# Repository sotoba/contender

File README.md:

# contender25

numpad for hardboot.

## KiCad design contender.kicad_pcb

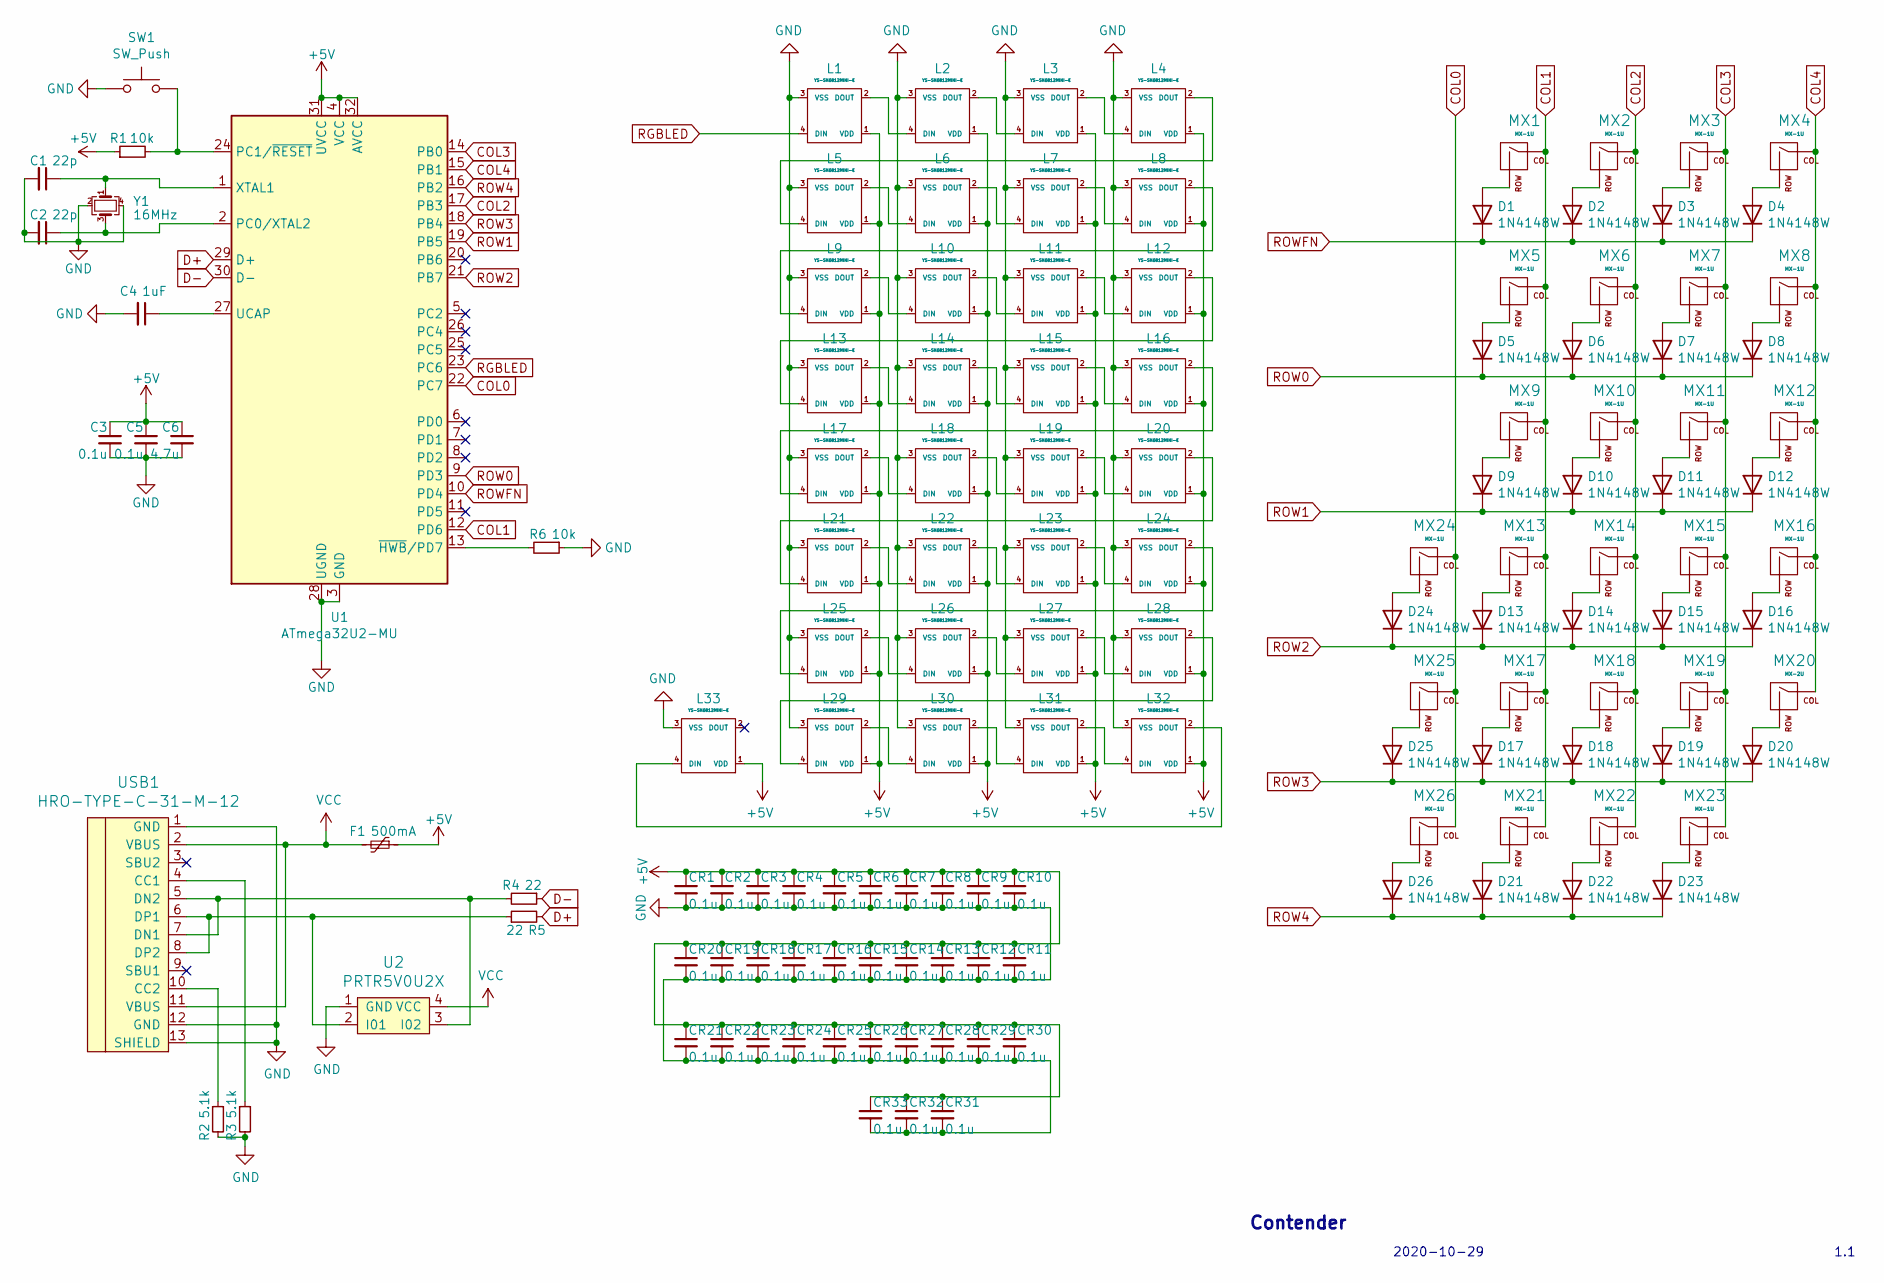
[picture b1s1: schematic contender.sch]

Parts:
C1, C2: 22p; C_0603_1608Metric
C3, C5: 0.1u; C_0603_1608Metric
C4: 1uF; C_0603_1608Metric
C6: 4.7u; C_0603_1608Metric
CR1, CR2, CR3, CR4, CR5, CR6, CR7, CR8, CR9, CR10, CR11, CR12, CR13, CR14, CR15, CR16, CR17, CR18, CR19, CR20, CR21, CR22, CR23, CR24, CR25, CR26, CR27, CR28, CR29, CR30, CR31, CR32, CR33: 0.1u; C_0603_1608Metric
D1, D2, D3, D4, D5, D6, D7, D8, D9, D10, D11, D12, D13, D14, D15, D16, D17, D18, D19, D20, D21, D22, D23, D24, D25, D26: 1N4148W; D_SOD-123
F1: 500mA; Fuse_1206_3216Metric
L1, L2, L3, L4, L5, L6, L7, L8, L9, L10, L11, L12, L13, L14, L15, L16, L17, L18, L19, L20, L21, L22, L23, L24, L25, L26, L27, L28, L29, L30, L31, L32, L33: YS-SK6812MINI-E; YS-SK6812-MINI-E_backlight
MX1, MX2, MX3, MX4, MX5, MX6, MX7, MX8, MX9, MX10, MX11, MX12, MX13, MX14, MX15, MX16, MX17, MX18, MX19, MX21, MX22, MX23, MX24, MX25, MX26: MX-1U; MXOnly-1U-Hotswap
MX20: MX-2U; MXOnly-2U-Hotswap-ReversedStabilizers
R1, R6: 10k; R_0805_2012Metric
R2, R3: 5.1k; R_0805_2012Metric
R4, R5: 22; R_0805_2012Metric
SW1: SW_Push; SKQG-1155865
U1: ATmega32U2-MU; QFN-32-1EP_5x5mm_Pitch0.5mm
U2: PRTR5V0U2X; SOT143B
USB1: HRO-TYPE-C-31-M-12; HRO-TYPE-C-31-M-12-Assembly
Y1: 16MHz; Crystal_SMD_3225-4Pin_3.2x2.5mm

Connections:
+5V: C3.1, C5.1, C6.1, CR1.1, CR2.1, CR3.1, CR4.1, CR5.1, CR6.1, CR7.1, CR8.1, CR9.1, CR10.1, CR11.1, CR12.1, CR13.1, CR14.1, CR15.1, CR16.1, CR17.1, CR18.1, CR19.1, CR20.1, CR21.1, CR22.1, CR23.1, CR24.1, CR25.1, CR26.1, CR27.1, CR28.1, CR29.1, CR30.1, CR31.1, CR32.1, CR33.1, F1.1, L1.1 (VDD), L2.1 (VDD), L3.1 (VDD), L4.1 (VDD), L5.1 (VDD), L6.1 (VDD), L7.1 (VDD), L8.1 (VDD), L9.1 (VDD), L10.1 (VDD), L11.1 (VDD), L12.1 (VDD), L13.1 (VDD), L14.1 (VDD), L15.1 (VDD), L16.1 (VDD), L17.1 (VDD), L18.1 (VDD), L19.1 (VDD), L20.1 (VDD), L21.1 (VDD), L22.1 (VDD), L23.1 (VDD), L24.1 (VDD), L25.1 (VDD), L26.1 (VDD), L27.1 (VDD), L28.1 (VDD), L29.1 (VDD), L30.1 (VDD), L31.1 (VDD), L32.1 (VDD), L33.1 (VDD), R1.1, U1.4 (VCC), U1.31 (UVCC), U1.32 (AVCC)
COL0: MX24.1 (COL), MX25.1 (COL), MX26.1 (COL), U1.22 (PC7)
COL1: MX1.1 (COL), MX5.1 (COL), MX9.1 (COL), MX13.1 (COL), MX17.1 (COL), MX21.1 (COL), U1.12 (PD6)
COL2: MX2.1 (COL), MX6.1 (COL), MX10.1 (COL), MX14.1 (COL), MX18.1 (COL), MX22.1 (COL), U1.17 (PB3)
COL3: MX3.1 (COL), MX7.1 (COL), MX11.1 (COL), MX15.1 (COL), MX19.1 (COL), MX23.1 (COL), U1.14 (PB0)
COL4: MX4.1 (COL), MX8.1 (COL), MX12.1 (COL), MX16.1 (COL), MX20.1 (COL), U1.15 (PB1)
D+: R5.2, U1.29 (D+)
D-: R4.1, U1.30 (D-)
GND: C1.2, C2.2, C3.2, C4.2, C5.2, C6.2, CR1.2, CR2.2, CR3.2, CR4.2, CR5.2, CR6.2, CR7.2, CR8.2, CR9.2, CR10.2, CR11.2, CR12.2, CR13.2, CR14.2, CR15.2, CR16.2, CR17.2, CR18.2, CR19.2, CR20.2, CR21.2, CR22.2, CR23.2, CR24.2, CR25.2, CR26.2, CR27.2, CR28.2, CR29.2, CR30.2, CR31.2, CR32.2, CR33.2, L1.3 (VSS), L2.3 (VSS), L3.3 (VSS), L4.3 (VSS), L5.3 (VSS), L6.3 (VSS), L7.3 (VSS), L8.3 (VSS), L9.3 (VSS), L10.3 (VSS), L11.3 (VSS), L12.3 (VSS), L13.3 (VSS), L14.3 (VSS), L15.3 (VSS), L16.3 (VSS), L17.3 (VSS), L18.3 (VSS), L19.3 (VSS), L20.3 (VSS), L21.3 (VSS), L22.3 (VSS), L23.3 (VSS), L24.3 (VSS), L25.3 (VSS), L26.3 (VSS), L27.3 (VSS), L28.3 (VSS), L29.3 (VSS), L30.3 (VSS), L31.3 (VSS), L32.3 (VSS), L33.3 (VSS), R2.2, R3.2, R6.1, SW1.1, U1.3 (GND), U1.28 (UGND), U1.33 (GND), U2.1 (GND), USB1.1 (GND), USB1.12 (GND), USB1.13 (SHIELD), Y1.2, Y1.4
unnamed: C1.1, U1.1 (XTAL1), Y1.1
unnamed: C2.1, U1.2 (PC0/XTAL2), Y1.3
unnamed: C4.1, U1.27 (UCAP)
unnamed: D1.2 (A), MX1.2 (ROW)
unnamed: D2.2 (A), MX2.2 (ROW)
unnamed: D3.2 (A), MX3.2 (ROW)
unnamed: D4.2 (A), MX4.2 (ROW)
unnamed: D5.2 (A), MX5.2 (ROW)
unnamed: D6.2 (A), MX6.2 (ROW)
unnamed: D7.2 (A), MX7.2 (ROW)
unnamed: D8.2 (A), MX8.2 (ROW)
unnamed: D9.2 (A), MX9.2 (ROW)
unnamed: D10.2 (A), MX10.2 (ROW)
unnamed: D11.2 (A), MX11.2 (ROW)
unnamed: D12.2 (A), MX12.2 (ROW)
unnamed: D13.2 (A), MX13.2 (ROW)
unnamed: D14.2 (A), MX14.2 (ROW)
unnamed: D15.2 (A), MX15.2 (ROW)
unnamed: D16.2 (A), MX16.2 (ROW)
unnamed: D17.2 (A), MX17.2 (ROW)
unnamed: D18.2 (A), MX18.2 (ROW)
unnamed: D19.2 (A), MX19.2 (ROW)
unnamed: D20.2 (A), MX20.2 (ROW)
unnamed: D21.2 (A), MX21.2 (ROW)
unnamed: D22.2 (A), MX22.2 (ROW)
unnamed: D23.2 (A), MX23.2 (ROW)
unnamed: D24.2 (A), MX24.2 (ROW)
unnamed: D25.2 (A), MX25.2 (ROW)
unnamed: D26.2 (A), MX26.2 (ROW)
unnamed: L1.2 (DOUT), L2.4 (DIN)
unnamed: L2.2 (DOUT), L3.4 (DIN)
unnamed: L3.2 (DOUT), L4.4 (DIN)
unnamed: L4.2 (DOUT), L5.4 (DIN)
unnamed: L5.2 (DOUT), L6.4 (DIN)
unnamed: L6.2 (DOUT), L7.4 (DIN)
unnamed: L7.2 (DOUT), L8.4 (DIN)
unnamed: L8.2 (DOUT), L9.4 (DIN)
unnamed: L10.2 (DOUT), L11.4 (DIN)
unnamed: L9.2 (DOUT), L10.4 (DIN)
unnamed: L11.2 (DOUT), L12.4 (DIN)
unnamed: L12.2 (DOUT), L13.4 (DIN)
unnamed: L13.2 (DOUT), L14.4 (DIN)
unnamed: L14.2 (DOUT), L15.4 (DIN)
unnamed: L15.2 (DOUT), L16.4 (DIN)
unnamed: L16.2 (DOUT), L17.4 (DIN)
unnamed: L17.2 (DOUT), L18.4 (DIN)
unnamed: L18.2 (DOUT), L19.4 (DIN)
unnamed: L19.2 (DOUT), L20.4 (DIN)
unnamed: L20.2 (DOUT), L21.4 (DIN)
unnamed: L21.2 (DOUT), L22.4 (DIN)
unnamed: L22.2 (DOUT), L23.4 (DIN)
unnamed: L23.2 (DOUT), L24.4 (DIN)
unnamed: L24.2 (DOUT), L25.4 (DIN)
unnamed: L25.2 (DOUT), L26.4 (DIN)
unnamed: L26.2 (DOUT), L27.4 (DIN)
unnamed: L27.2 (DOUT), L28.4 (DIN)
unnamed: L28.2 (DOUT), L29.4 (DIN)
unnamed: L29.2 (DOUT), L30.4 (DIN)
unnamed: L30.2 (DOUT), L31.4 (DIN)
unnamed: L31.2 (DOUT), L32.4 (DIN)
unnamed: L32.2 (DOUT), L33.4 (DIN)
unnamed: R1.2, SW1.2, U1.24 (PC1/~RESET)
unnamed: R2.1, USB1.10 (CC2)
unnamed: R3.1, USB1.4 (CC1)
unnamed: R4.2, U2.3 (I02), USB1.5 (DN2), USB1.7 (DN1)
unnamed: R5.1, U2.2 (I01), USB1.6 (DP1), USB1.8 (DP2)
unnamed: R6.2, U1.13 (~HWB~/PD7)
RGBLED: L1.4 (DIN), U1.23 (PC6)
ROW0: D5.1 (K), D6.1 (K), D7.1 (K), D8.1 (K), U1.9 (PD3)
ROW1: D9.1 (K), D10.1 (K), D11.1 (K), D12.1 (K), U1.19 (PB5)
ROW2: D13.1 (K), D14.1 (K), D15.1 (K), D16.1 (K), D24.1 (K), U1.21 (PB7)
ROW3: D17.1 (K), D18.1 (K), D19.1 (K), D20.1 (K), D25.1 (K), U1.18 (PB4)
ROW4: D21.1 (K), D22.1 (K), D23.1 (K), D26.1 (K), U1.16 (PB2)
ROWFN: D1.1 (K), D2.1 (K), D3.1 (K), D4.1 (K), U1.10 (PD4)
VCC: F1.2, U2.4 (VCC), USB1.2 (VBUS), USB1.11 (VBUS)

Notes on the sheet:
Contender
2020-10-29
1.1

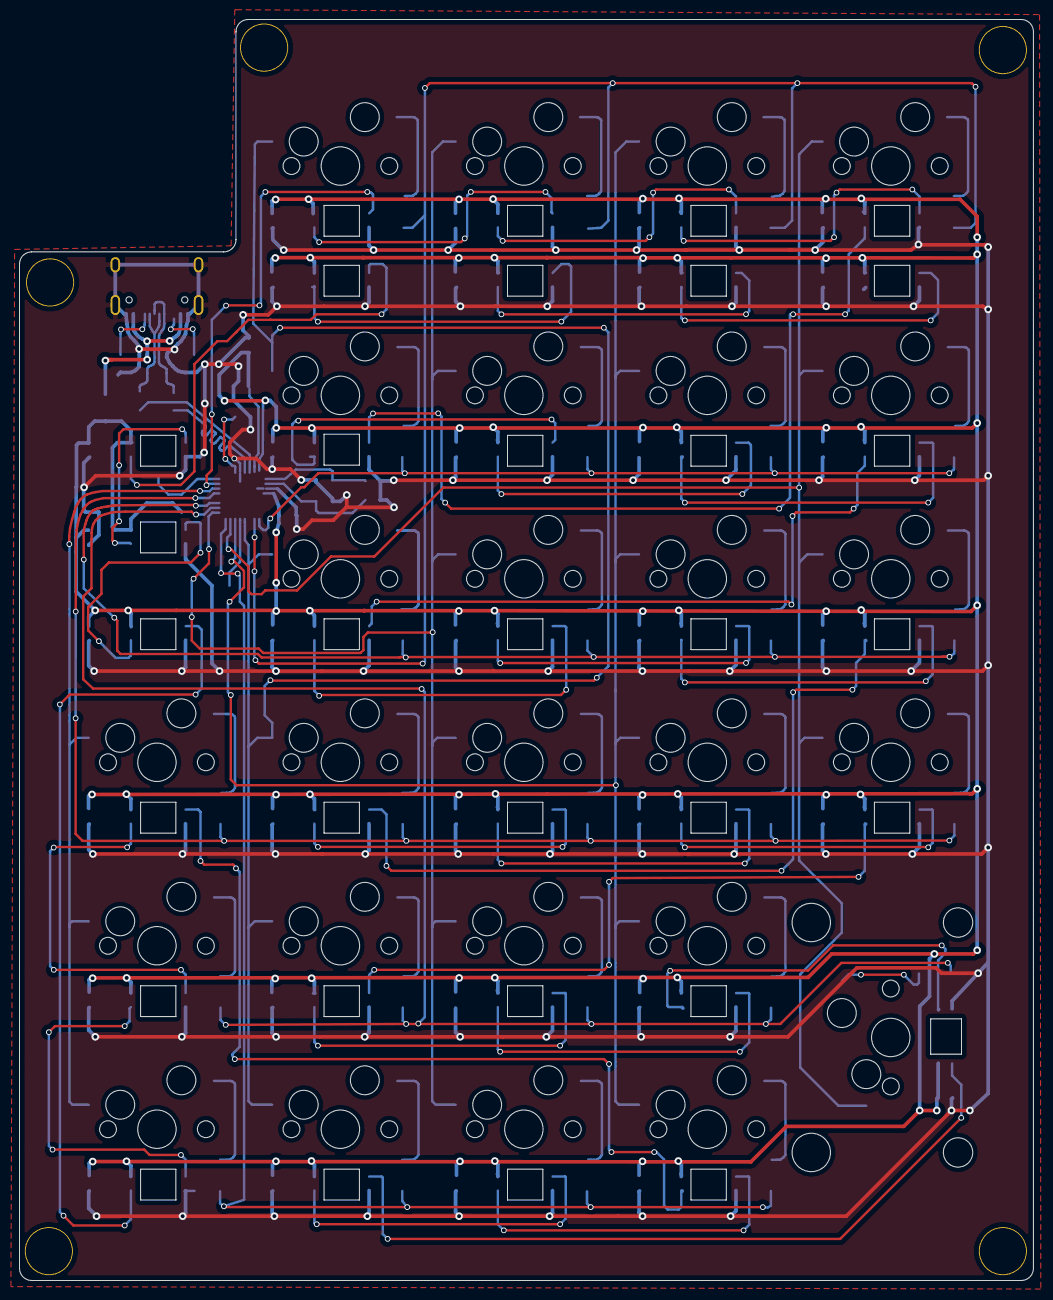
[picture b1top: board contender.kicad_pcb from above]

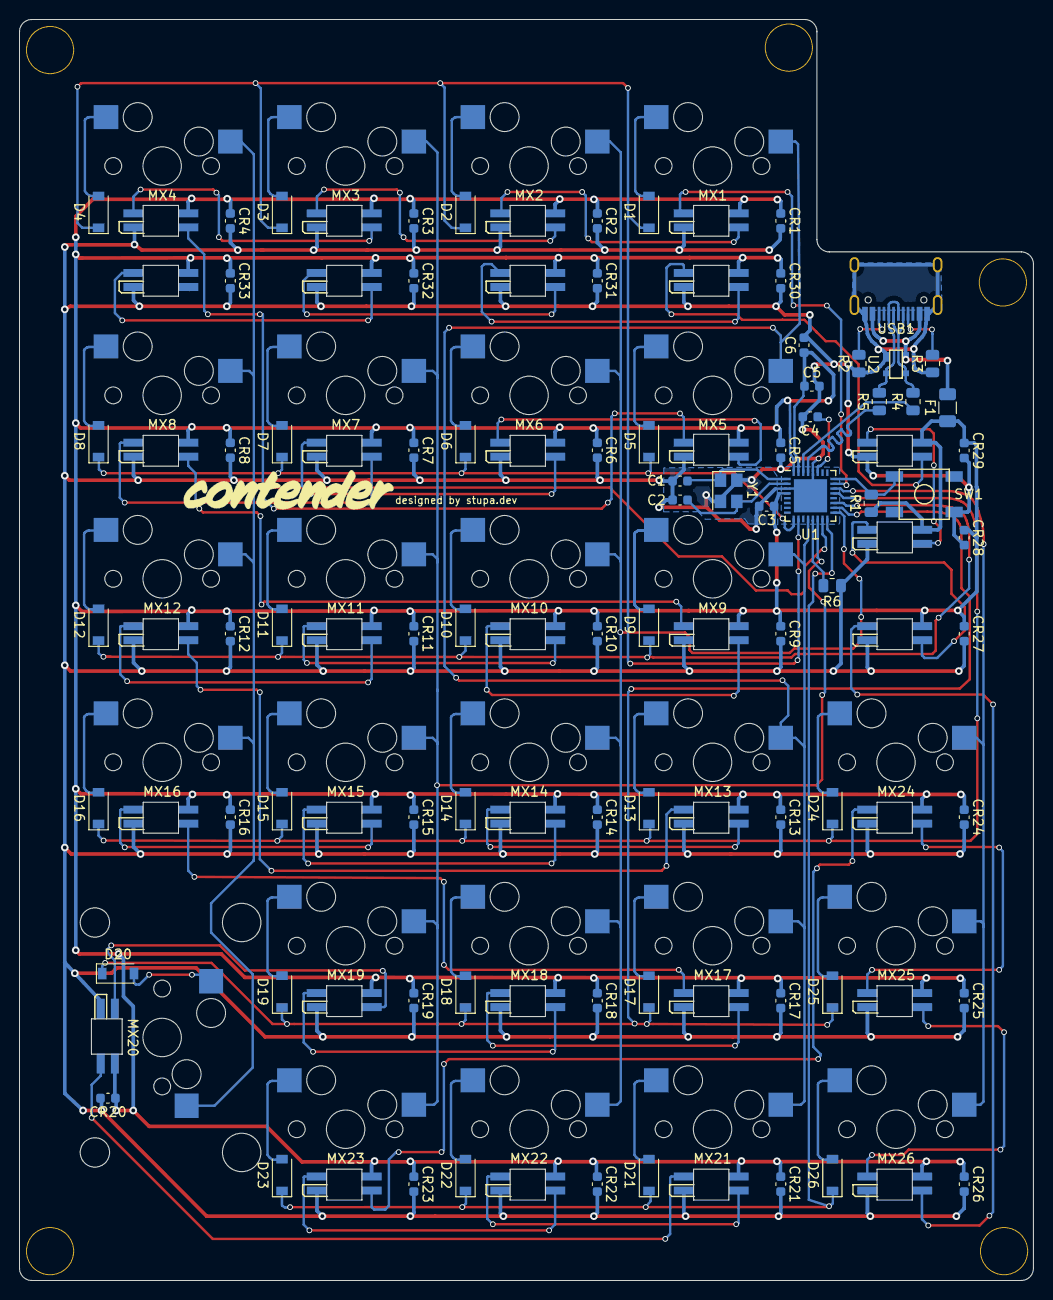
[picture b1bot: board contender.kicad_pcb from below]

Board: 2 copper layers, 105.3 x 130.9 mm, 141 parts (77 on the bottom side), 84 nets.

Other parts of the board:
HOLE_M3, HOLE_M3#2, HOLE_M3#3, HOLE_M3#4, HOLE_M3#5: VAL**; HOLE_M3

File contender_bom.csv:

"ID";"指定子";"パッケージ";"数量";"名称";"供給業者、参考資料";
1;"HOLE_M3,HOLE_M3,HOLE_M3,HOLE_M3,HOLE_M3";"HOLE_M3";5;"VAL**";;;
2;"MX21,MX26,MX25,MX24,MX23,MX22,MX19,MX18,MX17,MX16,MX15,MX14,MX13,MX12,MX11,MX10,MX9,MX8,MX7,MX6,MX5,MX4,MX3,MX2,MX1";"MXOnly-1U-Hotswap";25;"MX-1U";;;
3;"MX20";"MXOnly-2U-Hotswap-ReversedStabilizers";1;"MX-2U";;;
4;"U1";"QFN-32-1EP_5x5mm_Pitch0.5mm";1;"ATmega32U2-AU";;;
5;"Y1";"Crystal_SMD_3225-4Pin_3.2x2.5mm";1;"16MHz";;;
6;"USB1";"HRO-TYPE-C-31-M-12-Assembly";1;"HRO-TYPE-C-31-M-12";;;
7;"U2";"SOT143B";1;"PRTR5V0U2X";;;
8;"SW1";"SKQG-1155865";1;"SW_Push";;;
9;"R6,R1";"R_0805_2012Metric";2;"10k";;;
10;"R5,R4";"R_0805_2012Metric";2;"22";;;
11;"R3,R2";"R_0805_2012Metric";2;"5.1k";;;
12;"L33,L32,L31,L30,L29,L28,L27,L26,L25,L24,L23,L22,L21,L20,L19,L18,L17,L16,L15,L14,L13,L12,L11,L10,L9,L8,L7,L6,L5,L4,L3,L2,L1";"YS-SK6812_backlight";33;"YS-SK6812MINI-E";;;
13;"F1";"Fuse_1206_3216Metric";1;"500mA";;;
14;"D26,D25,D24,D23,D22,D21,D20,D19,D18,D17,D16,D15,D14,D13,D12,D11,D10,D9,D8,D7,D6,D5,D4,D3,D2,D1";"D_SOD-123";26;"1N4148W";;;
15;"CR33,CR32,CR31,CR30,CR29,CR28,CR27,CR26,CR25,CR24,CR23,CR22,CR21,CR20,CR19,CR18,CR17,CR16,CR15,CR14,CR13,CR12,CR11,CR10,CR9,CR8,CR7,CR6,CR5,CR4,CR3,CR2,CR1,C5,C3";"C_0603_1608Metric";35;"0.1u";;;
16;"C6";"C_0603_1608Metric";1;"4.7u";;;
17;"C4";"C_0603_1608Metric";1;"1uF";;;
18;"C2,C1";"C_0603_1608Metric";2;"22p";;;

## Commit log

2020-08-13 add project files
2020-08-13 add submodules
2020-08-13 add footprint libs
2020-09-13 add Type-C module
2020-10-06 rename & add lib
2020-10-17 fixup scheme
2020-11-06 1.0 finish up
2020-11-09 fix mounthole point
2020-12-29 add plates & gerber data
2020-12-31 fix led footpring & v1.1 commit
2021-09-30 production release
2021-10-02 copy build guide from craftwalk
2021-12-04 draft commit
2021-12-04 add header iamges
2021-12-04 fix README
